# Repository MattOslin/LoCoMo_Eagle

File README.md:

# LoCoMo

Eagle files for LoCoMo boards.

Motherboard is the breakout for ESP-12, including wiperboard, espboard, and usb board. The individual boards are the cut up sections. Note that the motherboard file is for reference only, and the individual boards are the only working copy.

Slipring is the slip ring/potentiometer.

Zigzag is an excellent sheet used to define the start and end points of the traces for the encoder. Look at the zigzag script to see how to format the output of the excel sheet for use in eagle.

DXF files for stencils can be created using the cream-dxf ulp.

The zip files are OSHPARK cam files.

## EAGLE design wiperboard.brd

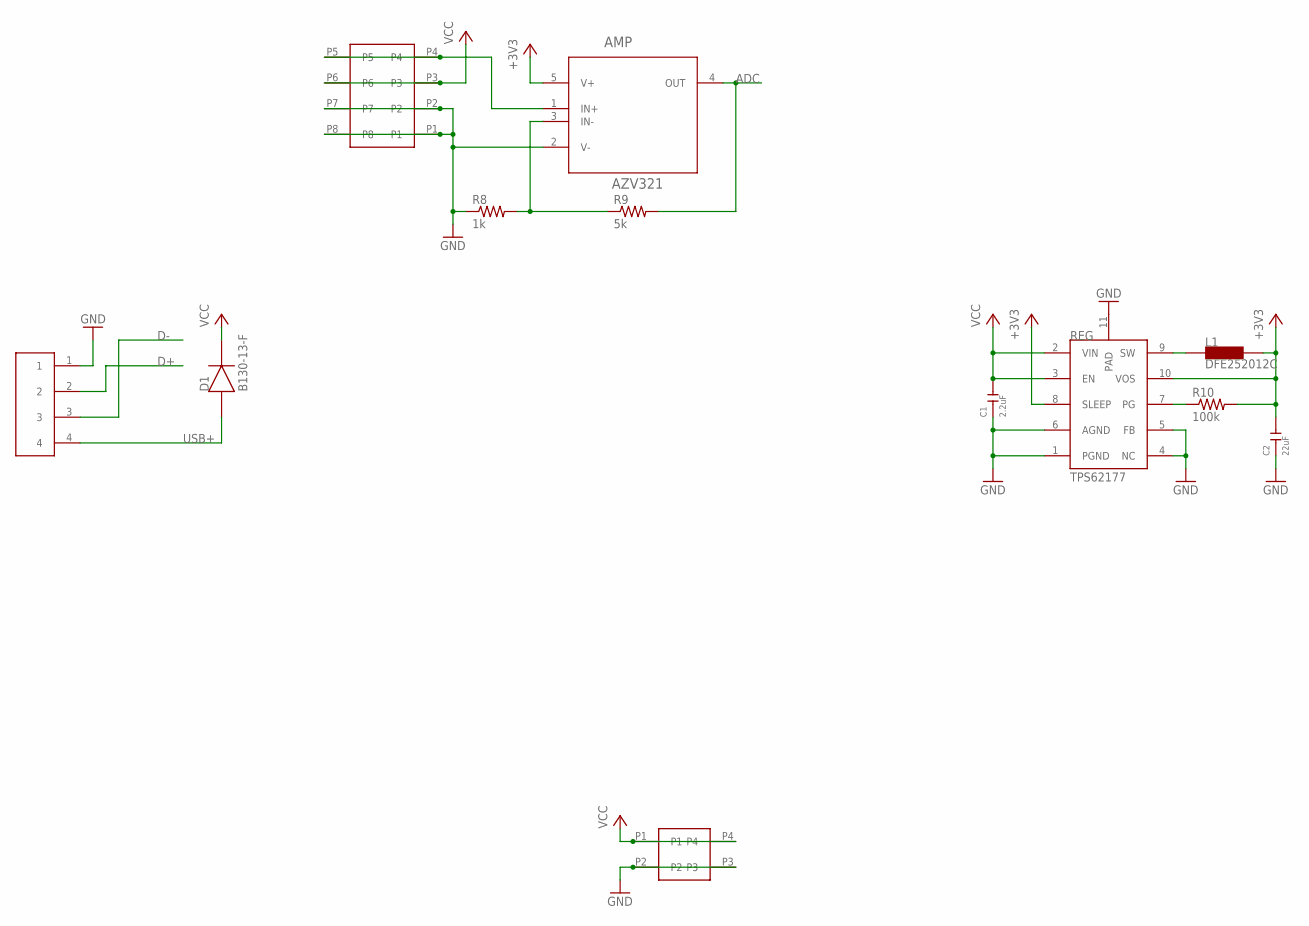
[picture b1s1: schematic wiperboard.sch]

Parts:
AMP: AZV321; SOT65P210X110-5N
C1: 2.2uF; C0603
C2: 22uF; C0603
CONN: BOURNS_2PIN
D1: B130-13-F; SMA
L1: DFE252012C; 1008
R8: 1k; R0603
R9: 5k; R0603
R10: 100k; R0603
REG: TPS62177; WSON-10
U$3: 4PIN_HEADER
WIPER: BOURNS_4PIN

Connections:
+3V3: AMP.5 (V+), C2.2, L1.P$3, R10.2, REG.8 (SLEEP), REG.10 (VOS)
ADC: AMP.4 (OUT), R9.2
D+: U$3.2
D-: U$3.3
GND: AMP.2 (V-), C1.1, C2.1, CONN.P2, CONN.P3, R8.1, REG.1 (PGND), REG.4 (NC), REG.5 (FB), REG.6 (AGND), REG.11 (PAD), U$3.1, WIPER.P1, WIPER.P2, WIPER.P7, WIPER.P8
unnamed: R10.1, REG.7 (PG)
unnamed: AMP.1 (IN+), WIPER.P4, WIPER.P5
unnamed: AMP.3 (IN-), R8.2, R9.1
SW: L1.P$2, REG.9 (SW)
USB+: D1.AN, U$3.4
VCC: C1.2, CONN.P1, CONN.P4, D1.CATH, REG.2 (VIN), REG.3 (EN), WIPER.P3, WIPER.P6

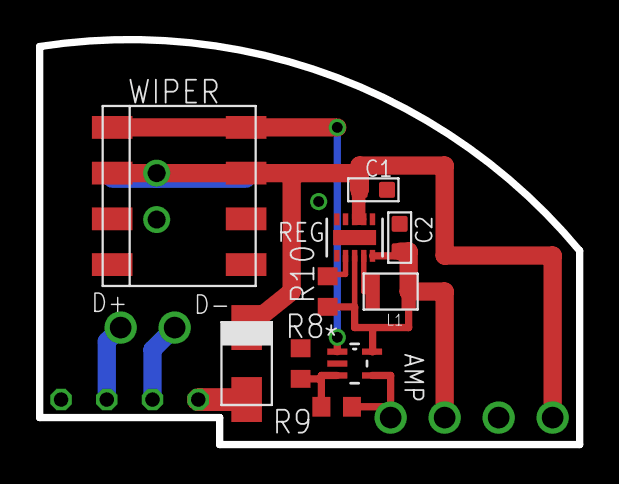
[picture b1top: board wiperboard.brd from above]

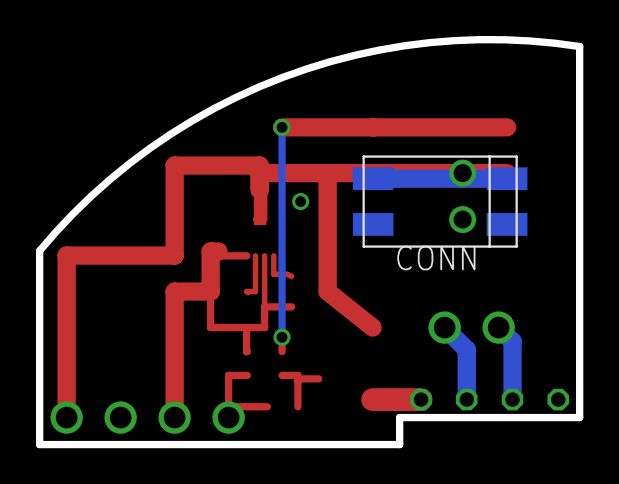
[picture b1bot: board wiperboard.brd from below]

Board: 2 copper layers, 30.0 x 22.5 mm, 12 parts (2 on the bottom side), 9 nets.

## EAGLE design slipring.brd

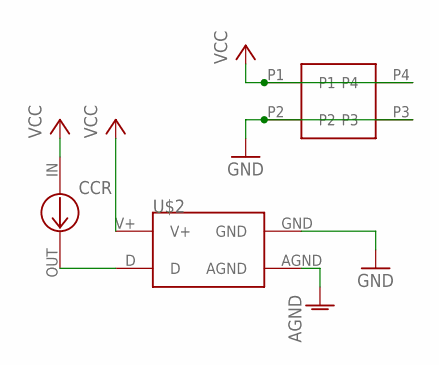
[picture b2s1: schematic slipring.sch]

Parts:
CCR: CCR
CONN: BOURNS_2PIN
U$2: RING3

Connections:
AGND: U$2.AGND
GND: CONN.P2, CONN.P3, U$2.GND
unnamed: CCR.OUT, U$2.D
VCC: CCR.IN, CONN.P1, CONN.P4, U$2.V+

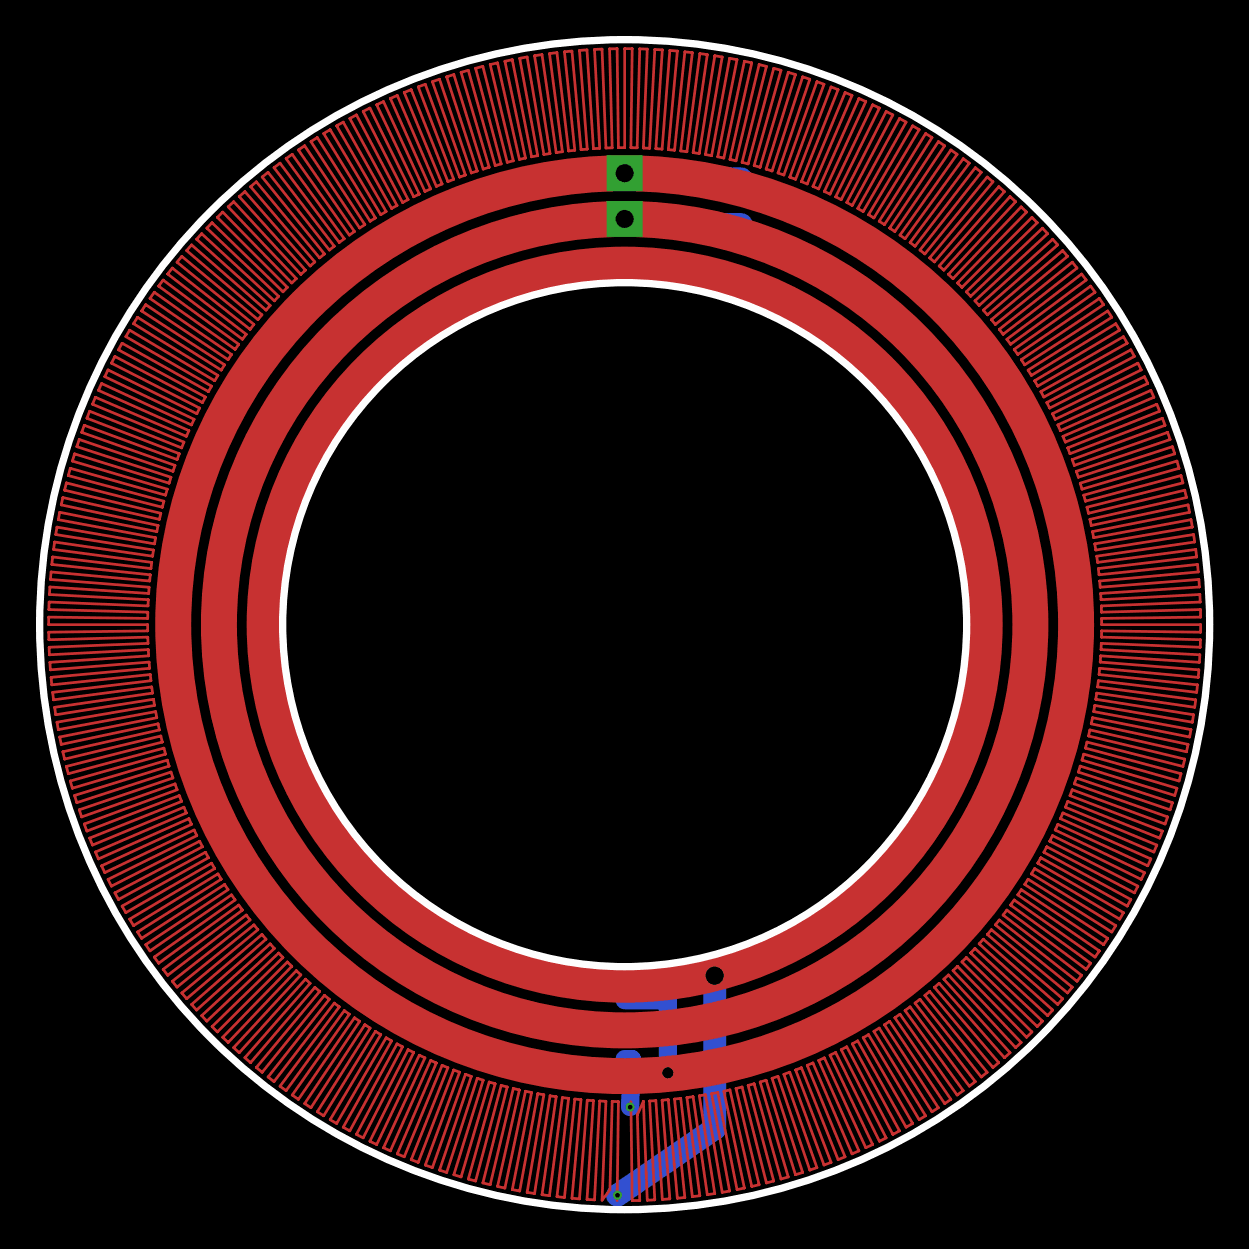
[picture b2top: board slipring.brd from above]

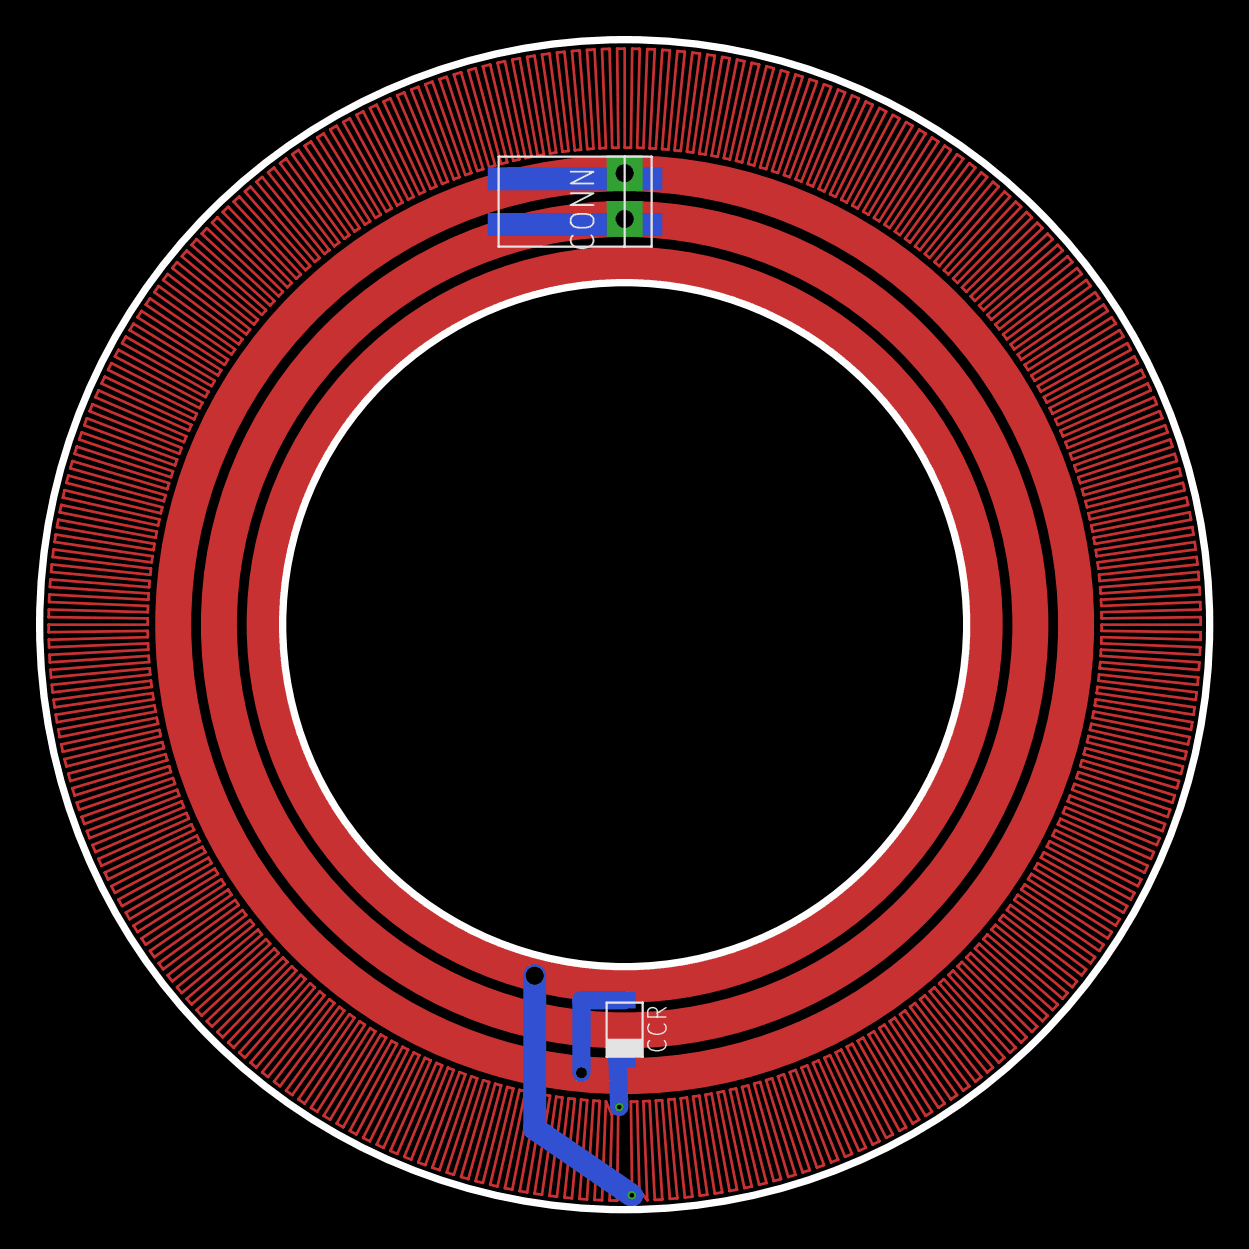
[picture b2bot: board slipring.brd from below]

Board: 2 copper layers, 65.0 x 65.0 mm, 3 parts (2 on the bottom side), 3 nets.

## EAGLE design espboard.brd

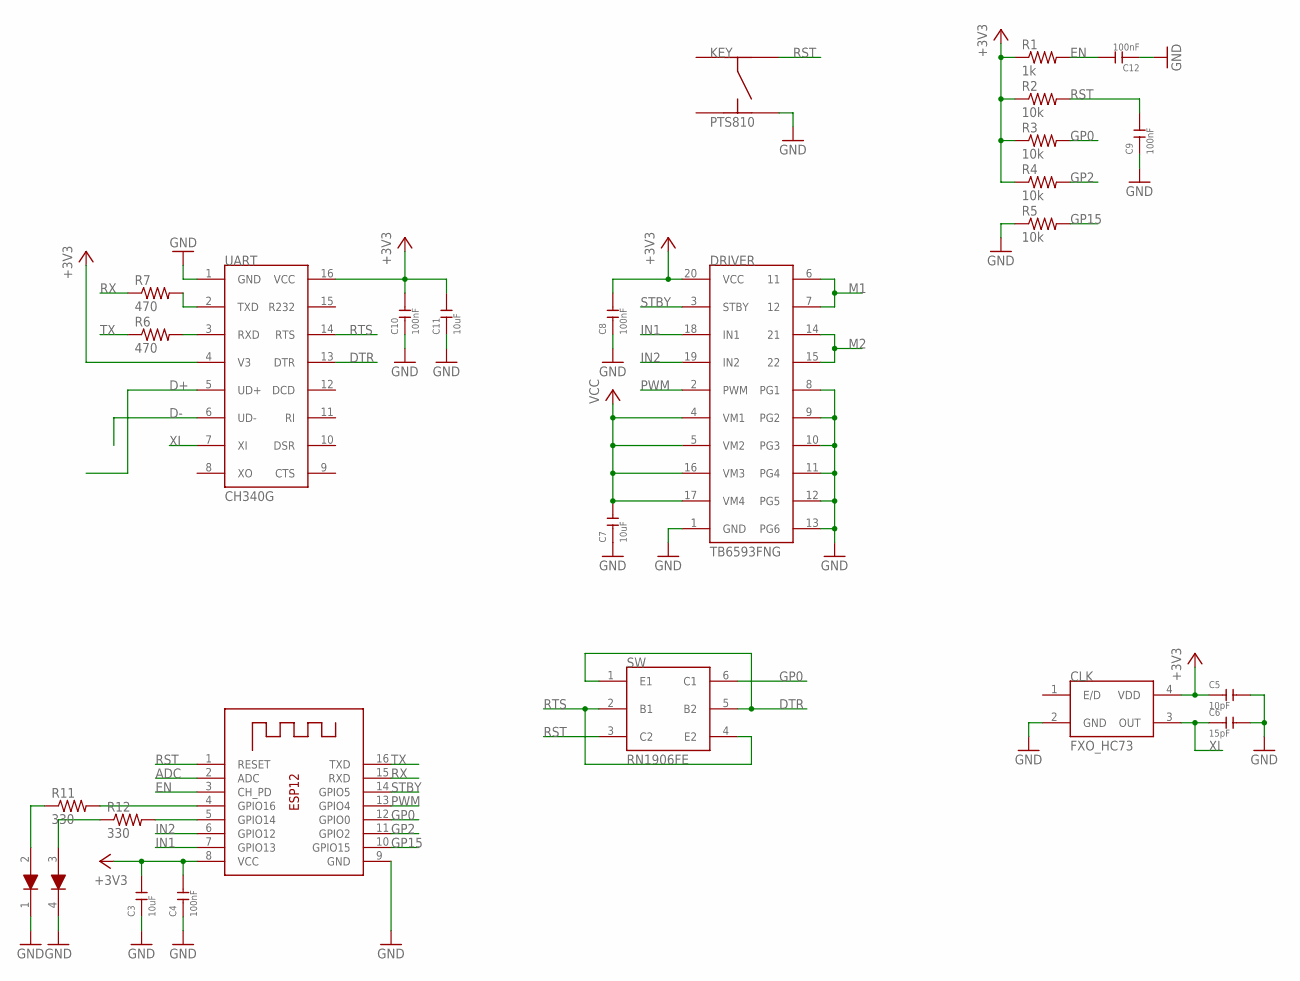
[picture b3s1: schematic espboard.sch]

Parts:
C3, C7, C11: 10uF; C0603
C4, C8, C9, C10, C12: 100nF; C0603
C5: 10pF; C0603
C6: 15pF; C0603
CLK: FXO_HC73; 4-SMD
DRIVER: TB6593FNG; SSOP-20
ESP12: ESP-12
KEY: PTS810; BUTTON
R1: 1k; R0603
R2, R3, R4, R5: 10k; R0603
R6, R7: 470; R0603
R11, R12: 330; R0603
SW: RN1906FE; SOT-563
U$2: BI_LED
UART: CH340G; 20-16

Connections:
+3V3: C3.2, C4.2, C5.1, C8.2, C10.2, C11.2, CLK.4 (VDD), DRIVER.20 (VCC), ESP12.8 (VCC), R1.1, R2.1, R3.1, R4.1, UART.4 (V3), UART.16 (VCC)
ADC: ESP12.2 (ADC)
D+: UART.5 (UD+)
D-: UART.6 (UD-)
DTR: SW.1 (E1), SW.5 (B2), UART.13 (DTR)
EN: C12.2, ESP12.3 (CH_PD), R1.2
GND: C3.1, C4.1, C5.2, C6.2, C7.1, C8.1, C9.1, C10.1, C11.1, C12.1, CLK.2 (GND), DRIVER.1 (GND), DRIVER.8 (PG1), DRIVER.9 (PG2), DRIVER.10 (PG3), DRIVER.11 (PG4), DRIVER.12 (PG5), DRIVER.13 (PG6), ESP12.9 (GND), KEY.4, R5.1, U$2.1, U$2.4, UART.1 (GND)
GP0: ESP12.12 (GPIO0), R3.2, SW.6 (C1)
GP2: ESP12.11 (GPIO2), R4.2
GP15: ESP12.10 (GPIO15), R5.2
IN1: DRIVER.18 (IN1), ESP12.7 (GPIO13)
IN2: DRIVER.19 (IN2), ESP12.6 (GPIO12)
M1: DRIVER.6 (11), DRIVER.7 (12)
M2: DRIVER.14 (21), DRIVER.15 (22)
unnamed: R7.2, UART.2 (TXD)
unnamed: R6.2, UART.3 (RXD)
unnamed: ESP12.5 (GPIO14), R12.2
unnamed: ESP12.4 (GPIO16), R11.2
unnamed: R11.1, U$2.2
unnamed: R12.1, U$2.3
PWM: DRIVER.2 (PWM), ESP12.13 (GPIO4)
RST: C9.2, ESP12.1 (RESET), KEY.2, R2.2, SW.3 (C2)
RTS: SW.2 (B1), SW.4 (E2), UART.14 (RTS)
RX: ESP12.15 (RXD), R7.1
STBY: DRIVER.3 (STBY), ESP12.14 (GPIO5)
TX: ESP12.16 (TXD), R6.1
VCC: C7.2, DRIVER.4 (VM1), DRIVER.5 (VM2), DRIVER.16 (VM3), DRIVER.17 (VM4)
XI: C6.1, CLK.3 (OUT), UART.7 (XI)

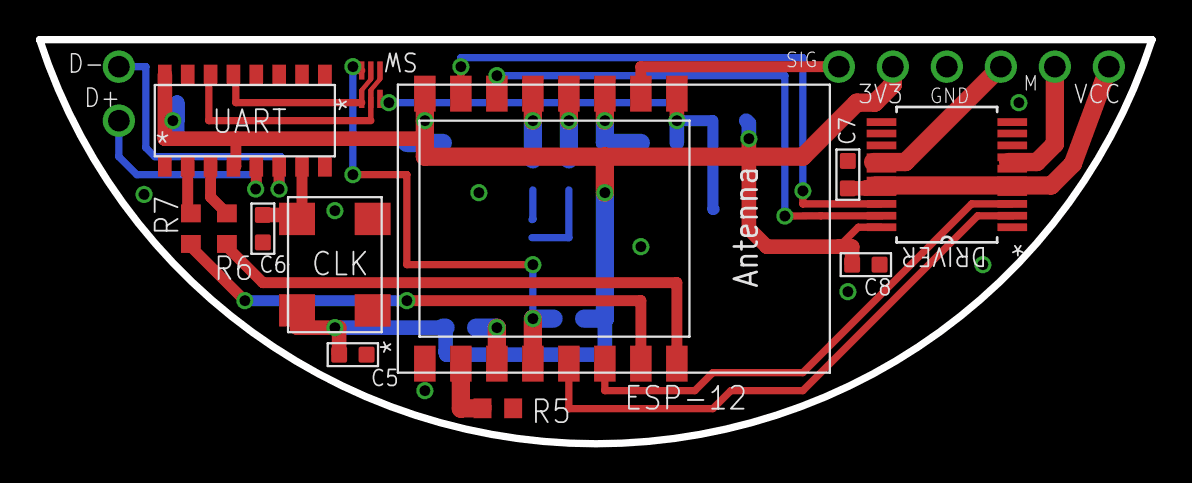
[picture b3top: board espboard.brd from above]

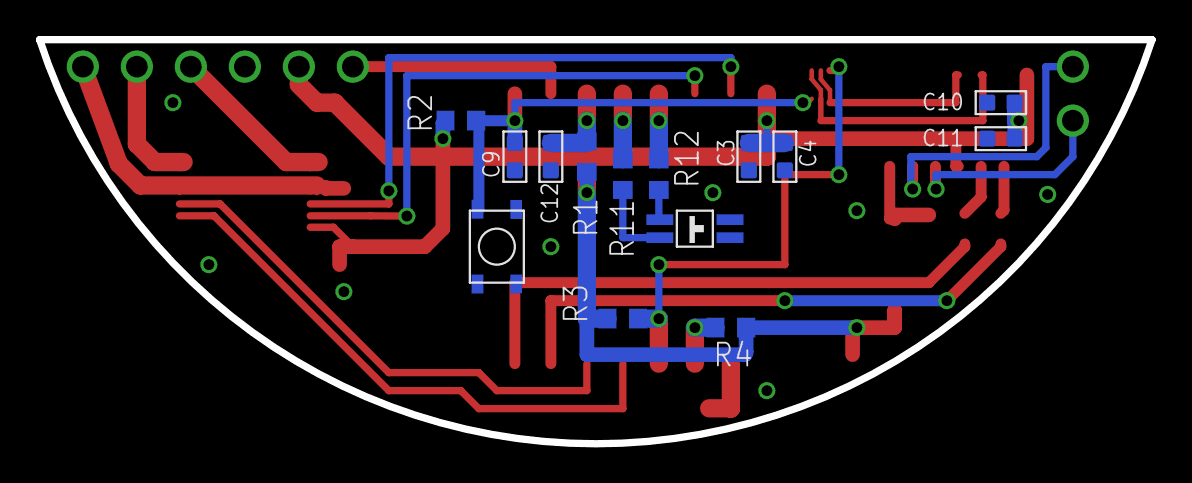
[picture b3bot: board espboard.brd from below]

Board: 2 copper layers, 61.8 x 22.5 mm, 26 parts (14 on the bottom side), 25 nets.

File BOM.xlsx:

Item | Module Quantity | Unit Price | Unit Price @10 | Total | Digikey # | URL | NOTES
4 Position Wiper | 1 | 1.26 | 1.145 | 1.145 | 70AAJ-4-M0-ND | https://www.digikey.com/product-detail/en/bourns-inc/70AAJ-4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
Op amp | 1 | 0.43 | 0.34899999999999998 | 0.34899999999999998 | AZV321KSTR-G1DICT-ND | http://www.digikey.com/scripts/DkSearch/dksus.dll?Detail&ite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
2 Position contact | 2 | 0.86 | 0.75900000000000001 | 1.518 | 70AAJ-2-M0-ND | https://www.digikey.com/product-detail/en/bourns-inc/70AAJ-2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
Motor driver | 1 | 1.33 | 1.181 | 1.181 | TB6593FNGCT-ND | http://www.digikey.com/scripts/DkSearch/dksus.dll?Detail&ite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
Inductor | 1 | 0.21 | 0.192 | 0.192 | 490-10563-1-ND | http://www.digikey.com/scripts/DkSearch/dksus.dll?Detail&ite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
Vertical mini usb | 1 | 1.04 | 0.91800000000000004 | 0.91800000000000004 | H125262-ND | https://www.digikey.com/product-detail/en/hirose-electric-co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
Regulator | 1 | 1.59 | 1.425 | 1.425 | 296-41856-1-ND | http://www.digikey.com/scripts/DkSearch/dksus.dll?Detail&ite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
Switch | 1 | 0.25 | 0.23200000000000001 | 0.23200000000000001 | RN1906FELF(CTCT-ND | http://www.digikey.com/scripts/DkSearch/dksus.dll?Detail&ite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
Power diode | 1 | 0.36 | 0.29099999999999998 | 0.29099999999999998 | B130-FDICT-ND | http://www.digikey.com/scripts/DkSearch/dksus.dll?Detail&ite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
Bi-LED | 1 | 0.44 | 0.311 | 0.311 | 160-2026-1-ND | http://www.digikey.com/product-detail/en/lite-on-inc/LTST-C2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
CCR | 1 | 0.44 | 0.374 | 0.374 | NSI45020AT1GOSCT-ND | https://www.digikey.com/product-detail/en/on-semiconductor/N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
Button | 1 | 0.28000000000000003 | 0.26800000000000002 | 0.26800000000000002 | CKN10502CT-ND | https://www.digikey.com/product-detail/en/c-k/PTS810-SJM-250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
Clock | 1 | 1.1100000000000001 | 0.98399999999999999 | 0.98399999999999999 | 631-1116-1-ND | http://www.digikey.com/scripts/DkSearch/dksus.dll?Detail&ite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
Header pins | 1 | 0.56000000000000005 | 0.38900000000000001 | 0.38900000000000001 | S9014E-04-ND | https://www.digikey.com/product-detail/en/sullins-connector-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
CH340G | 1 | 0.5 | 0.25 | 0.25 |  | EBAY
ESP12 | 1 | 2 | 1 | 1
1K Resistor | 2 |  |  |  |  |  | STOCK
5.1K Resistor | 1
330Ohm Resistor | 2
10K Resistor | 5 |  |  |  |  |  | STOCK
470Ohm Resistor | 2
100nF Capacitor | 5
10uF Capacitor | 3
2.2uF Capacitor | 1 |  |  |  |  |  | STOCK
22uF Capacitor | 1 |  |  |  |  |  | STOCK
10pF Capacitor | 1 |  |  |  |  |  | STOCK
15pF Capacitor | 1
 |  |  |  | 10.827

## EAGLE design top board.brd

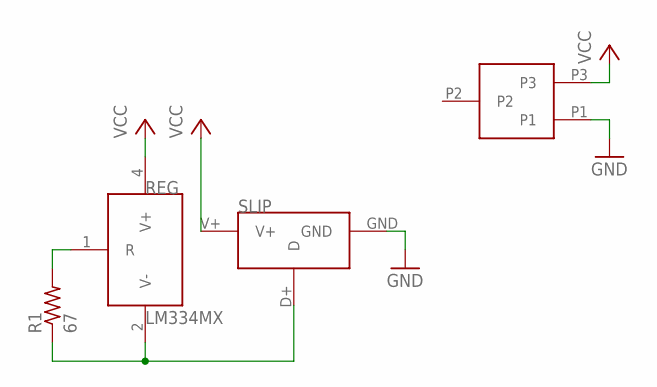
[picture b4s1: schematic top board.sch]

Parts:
R1: 67; R0603
REG: LM334MX; 8-SOIC
SLIP: RING
U$2: AVX_CONN

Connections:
GND: SLIP.GND, U$2.P1
unnamed: R1.2, REG.1 (R)
unnamed: R1.1, REG.2 (V-), SLIP.D+ (D)
VCC: REG.4 (V+), SLIP.V+, U$2.P3

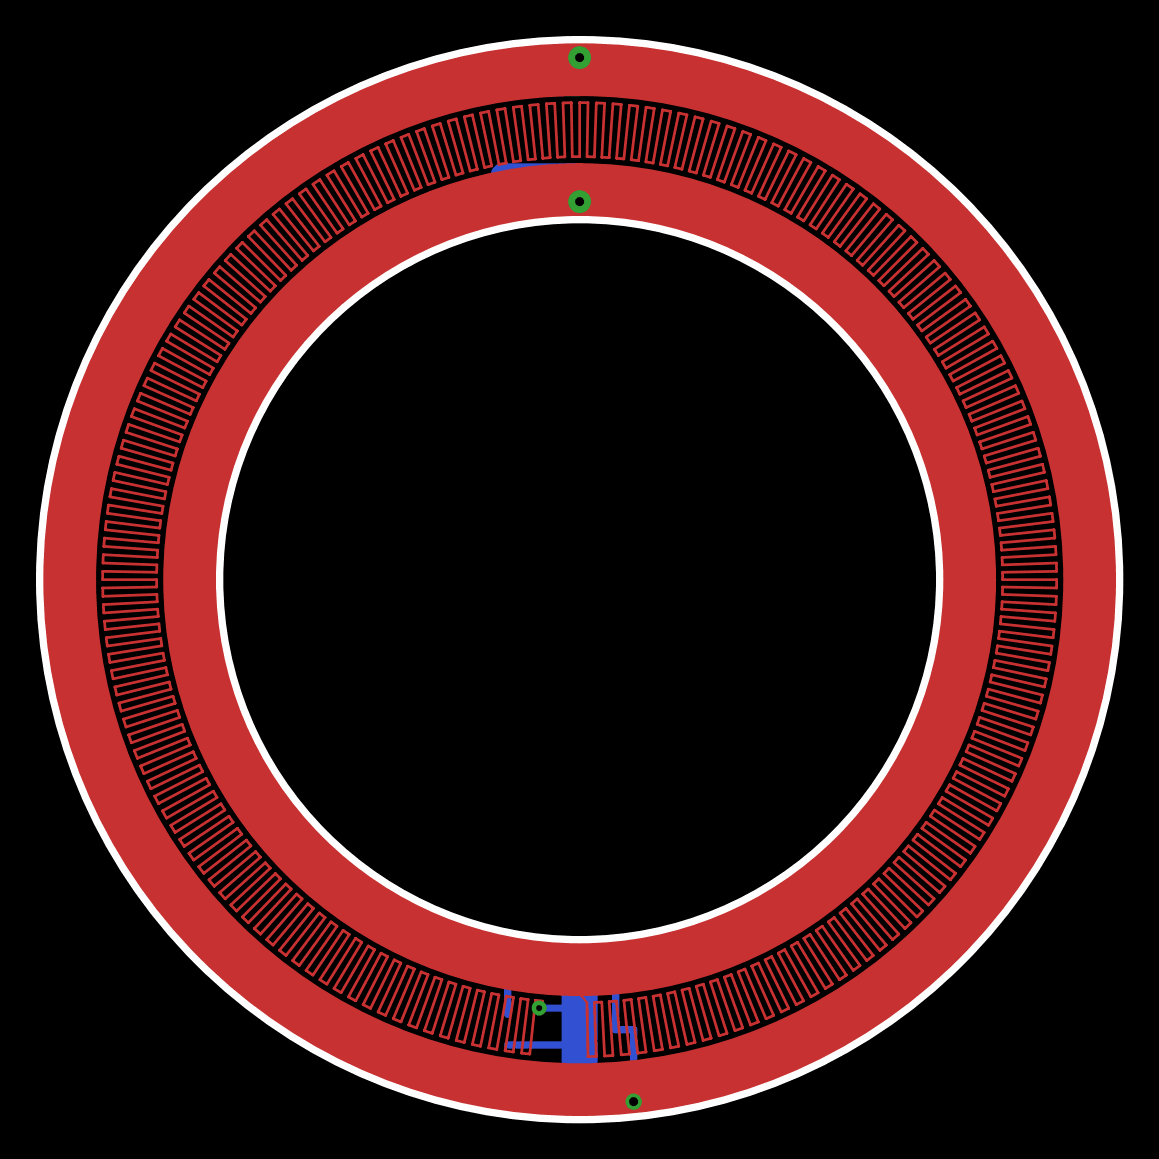
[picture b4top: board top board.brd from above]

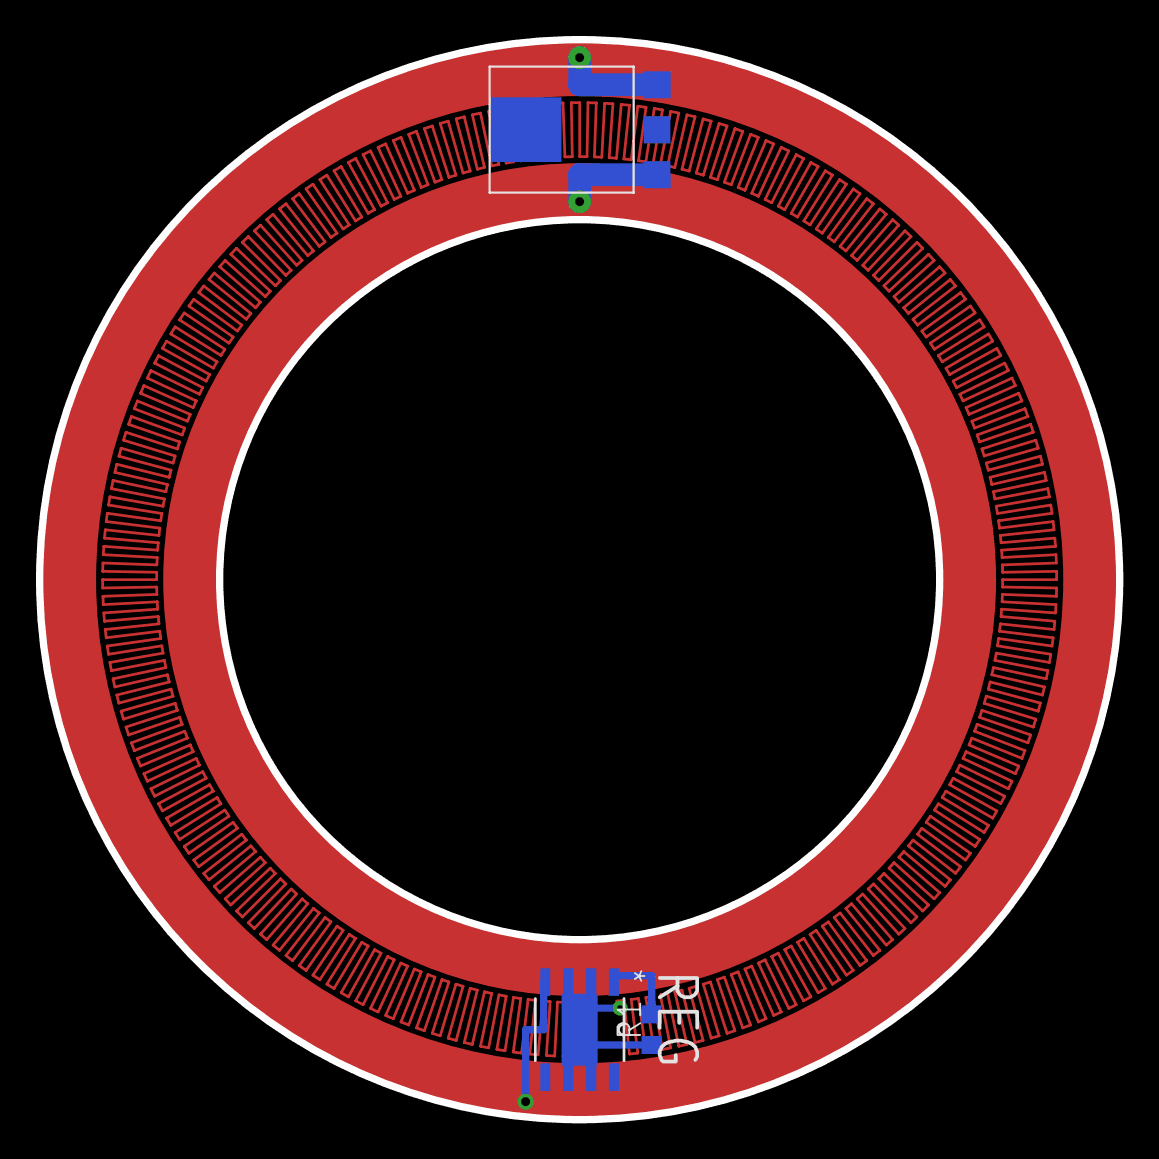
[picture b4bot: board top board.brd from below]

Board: 2 copper layers, 60.0 x 60.0 mm, 4 parts (3 on the bottom side), 4 nets.

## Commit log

2016-11-05 pdf schematic
2016-11-10 began routing
2016-11-12 finished routing and made gerber files
2016-11-14 added logo, optimized ground pours
2016-12-18 fixed motherboard after initial tests
2017-03-28 Add files via upload
    Final version of gen1 boards, added initial cad of slipring with analog ground, switching to bourns connectors
2017-03-28 started work on revised board
2017-03-28 switched to 20mA reg
2017-04-01 more routing
2017-04-03 final routing before splitting up boards
2017-04-03 split board into three parts, cam processed
2017-04-04 final cad for purchase
2017-04-18 Added BOM, updated resistor values
2017-04-18 updated bom
2017-05-17 fixed intial board errors, including short, flipped usb, and missing trace
2017-05-24 fixed collision issue
